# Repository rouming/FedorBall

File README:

NAME
    FedorBall -- is a toy-ball which detects current top position
    with accelerometer MMA7455 and turns on leds in special order
    using 4 led drivers TLC5940.

USED MATERIALS
    ATMEGA16
        http://www.atmel.com/Images/doc2466.pdf
        http://www.atmel.com/Images/doc8453.pdf
        http://www.tty1.net/blog/2008-04-29-avr-gcc-optimisations_en.html

    TLC5940
        http://code.google.com/p/tlc5940arduino/
        http://www.ti.com/lit/ds/symlink/tlc5940.pdf

    MMA7455
        http://arduino.cc/playground/Main/MMA7455
        http://www.freescale.com/files/sensors/doc/app_note/AN3468.pdf
        http://cache.freescale.com/files/sensors/doc/data_sheet/MMA7455L.pdf?fpsp=1

    TWI(I2C)
        http://easyelectronics.ru/avr-uchebnyj-kurs-ispolzovanie-avr-twi-dlya-raboty-s-shinoj-iic-i2c.html

    DODECAHEDRON INFO
        http://ru.wikipedia.org/wiki/Додекаэдр
        http://www.maths.surrey.ac.uk/hosted-sites/R.Knott/Fibonacci/phi3DGeom.html

    RAY-TRIANGLE INTERSECTION
        http://jgt.akpeters.com/papers/MollerTrumbore97/

    FIXED POINT
        http://gcc.gnu.org/wiki/FixedPointArithmetic
        http://x86asm.net/articles/fixed-point-arithmetic-and-tricks/

    OPENGL
        http://www.songho.ca/opengl/gl_vertexarray.html

AUTHOR
    Roman Pen

USERS
    son Fedor

ACKNOWLEDGEMENTS
COPYRIGHT & LICENSE
    Copyright 2012 Roman Pen

    This program is free software; you can redistribute it and/or modify it
    under the terms of either: the GNU General Public License as published
    by the Free Software Foundation

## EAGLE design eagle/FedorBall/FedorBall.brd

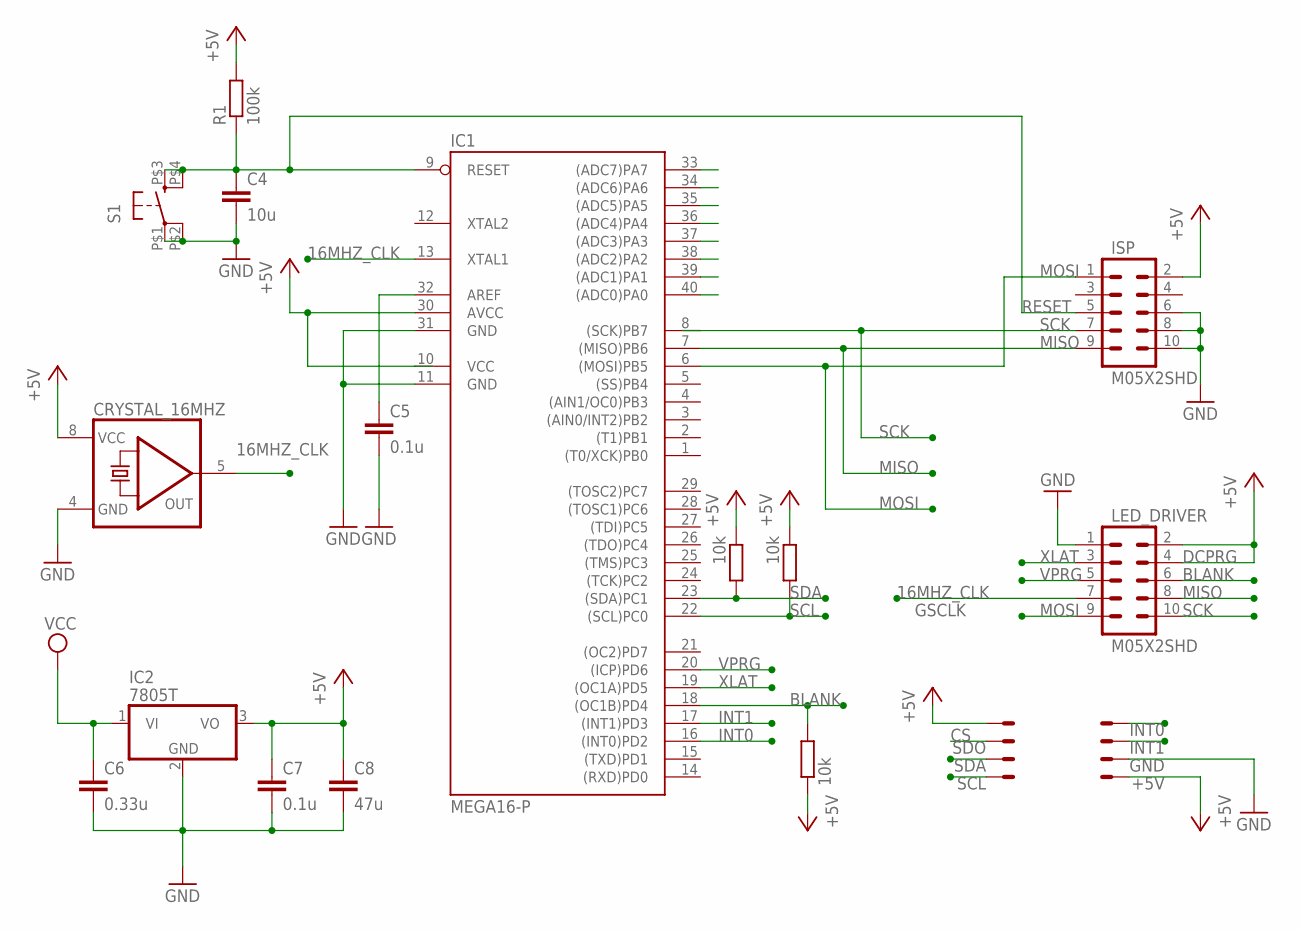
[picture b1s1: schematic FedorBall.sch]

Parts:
C4: 10u; C050-024X044
C5, C7: 0.1u; C050-024X044
C6: 0.33u; C050-024X044
C8: 47u; C050-024X044
CRYSTAL_16MHZ: QG5460; DIL08S
IC1: MEGA16-P; DIL40
IC2: 7805T; TO220H
ISP: M05X2SHD; 2X5-SHROUDED
LED_DRIVER: M05X2SHD; 2X5-SHROUDED
R1: 100k; 0207/10
R2, R5, R6: 10k; 0207/10
S1: TAC_SWITCHKSA_SEALED; KSA_SEALED_TAC_SWITCH
X1, X2: 22-23-2041

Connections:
16MHZ_CLK: CRYSTAL_16MHZ.5 (OUT), IC1.13 (XTAL1), LED_DRIVER.7
+5V: C7.1, C8.1, CRYSTAL_16MHZ.8 (VCC), IC1.10 (VCC), IC1.30 (AVCC), IC2.3 (VO), ISP.2, LED_DRIVER.2, LED_DRIVER.4, R1.2, R2.1, R5.1, R6.1, X1.1, X2.4
BLANK: IC1.18 ((OC1B)PD4), LED_DRIVER.6, R2.2
GND: C4.2, C5.2, C6.2, C7.2, C8.2, CRYSTAL_16MHZ.4 (GND), IC1.11 (GND), IC1.31 (GND), IC2.2 (GND), ISP.6, ISP.8, ISP.10, LED_DRIVER.1, S1.P$1 (1), S1.P$2 (2), X1.2
INT0: IC1.16 ((INT0)PD2), X1.4
INT1: IC1.17 ((INT1)PD3), X1.3
MISO: IC1.7 ((MISO)PB6), ISP.9, LED_DRIVER.8
MOSI: IC1.6 ((MOSI)PB5), ISP.1, LED_DRIVER.9
unnamed: C5.1, IC1.32 (AREF)
unnamed: C4.1, IC1.9 (RESET), ISP.5, R1.1, S1.P$3 (3), S1.P$4 (4)
SCK: IC1.8 ((SCK)PB7), ISP.7, LED_DRIVER.10
SCL: IC1.22 ((SCL)PC0), R6.2, X2.1
SDA: IC1.23 ((SDA)PC1), R5.2, X2.2
SDO: X2.3
VCC: C6.1, IC2.1 (VI)
VPRG: IC1.20 ((ICP)PD6), LED_DRIVER.5
XLAT: IC1.19 ((OC1A)PD5), LED_DRIVER.3

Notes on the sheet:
DCPRG
SCK
MISO
MOSI
RESET
GSCLK

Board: 2 copper layers, 17 parts (15 on the bottom side), 16 nets, no tracks yet.

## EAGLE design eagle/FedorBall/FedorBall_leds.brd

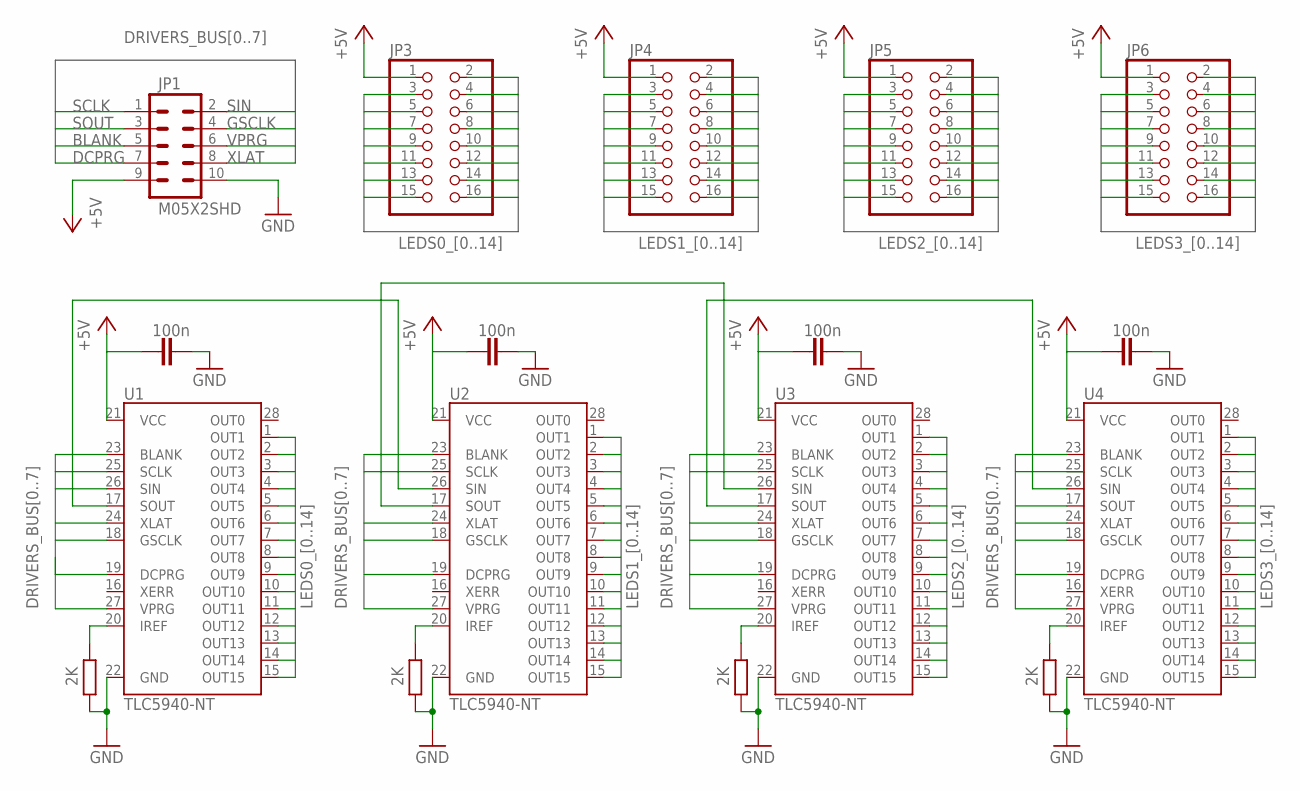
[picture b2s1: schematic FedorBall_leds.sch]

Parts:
C1, C2, C3, C4: 100n; C025-024X044
JP1: M05X2SHD; 2X5-SHROUDED
JP3, JP4, JP5, JP6: PINHD-2X8; 2X08
R1, R2, R3, R4: 2K; 0204/5
U1, U2, U3, U4: TLC5940-NT; DIL28-3

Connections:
+5V: C1.1, C2.1, C3.1, C4.1, JP1.9, JP3.1, JP4.1, JP5.1, JP6.1, U1.21 (VCC), U2.21 (VCC), U3.21 (VCC), U4.21 (VCC)
DRIVERS_BUS0: JP1.5, U1.23 (BLANK), U2.23 (BLANK), U3.23 (BLANK), U4.23 (BLANK)
DRIVERS_BUS1: JP1.1, U1.25 (SCLK), U2.25 (SCLK), U3.25 (SCLK)
DRIVERS_BUS2: JP1.2, U1.26 (SIN)
DRIVERS_BUS3: JP1.3, U4.17 (SOUT)
DRIVERS_BUS4: JP1.8, U1.24 (XLAT), U2.24 (XLAT), U3.24 (XLAT), U4.24 (XLAT)
DRIVERS_BUS5: JP1.4, U1.18 (GSCLK), U2.18 (GSCLK), U3.18 (GSCLK), U4.18 (GSCLK)
DRIVERS_BUS6: JP1.7, U1.19 (DCPRG), U2.19 (DCPRG), U3.19 (DCPRG), U4.19 (DCPRG)
DRIVERS_BUS7: JP1.6, U1.27 (VPRG), U2.27 (VPRG), U3.27 (VPRG), U4.27 (VPRG)
GND: C1.2, C2.2, C3.2, C4.2, JP1.10, R1.1, R2.1, R3.1, R4.1, U1.22 (GND), U2.22 (GND), U3.22 (GND), U4.22 (GND)
LEDS0_0: JP3.16, U1.1 (OUT1)
LEDS0_1: JP3.15, U1.2 (OUT2)
LEDS0_2: JP3.14, U1.3 (OUT3)
LEDS0_3: JP3.13, U1.4 (OUT4)
LEDS0_4: JP3.12, U1.5 (OUT5)
LEDS0_5: JP3.11, U1.6 (OUT6)
LEDS0_6: JP3.10, U1.7 (OUT7)
LEDS0_7: JP3.9, U1.8 (OUT8)
LEDS0_8: JP3.8, U1.9 (OUT9)
LEDS0_9: JP3.7, U1.10 (OUT10)
LEDS0_10: JP3.6, U1.11 (OUT11)
LEDS0_11: JP3.5, U1.12 (OUT12)
LEDS0_12: JP3.4, U1.13 (OUT13)
LEDS0_13: JP3.3, U1.14 (OUT14)
LEDS0_14: JP3.2, U1.15 (OUT15)
LEDS1_0: JP4.16, U2.1 (OUT1)
LEDS1_1: JP4.15, U2.2 (OUT2)
LEDS1_2: JP4.14, U2.3 (OUT3)
LEDS1_3: JP4.13, U2.4 (OUT4)
LEDS1_4: JP4.12, U2.5 (OUT5)
LEDS1_5: JP4.11, U2.6 (OUT6)
LEDS1_6: JP4.10, U2.7 (OUT7)
LEDS1_7: JP4.9, U2.8 (OUT8)
LEDS1_8: JP4.8, U2.9 (OUT9)
LEDS1_9: JP4.7, U2.10 (OUT10)
LEDS1_10: JP4.6, U2.11 (OUT11)
LEDS1_11: JP4.5, U2.12 (OUT12)
LEDS1_12: JP4.4, U2.13 (OUT13)
LEDS1_13: JP4.3, U2.14 (OUT14)
LEDS1_14: JP4.2, U2.15 (OUT15)
LEDS2_0: JP5.16, U3.1 (OUT1)
LEDS2_1: JP5.15, U3.2 (OUT2)
LEDS2_2: JP5.14, U3.3 (OUT3)
LEDS2_3: JP5.13, U3.4 (OUT4)
LEDS2_4: JP5.12, U3.5 (OUT5)
LEDS2_5: JP5.11, U3.6 (OUT6)
LEDS2_6: JP5.10, U3.7 (OUT7)
LEDS2_7: JP5.9, U3.8 (OUT8)
LEDS2_8: JP5.8, U3.9 (OUT9)
LEDS2_9: JP5.7, U3.10 (OUT10)
LEDS2_10: JP5.6, U3.11 (OUT11)
LEDS2_11: JP5.5, U3.12 (OUT12)
LEDS2_12: JP5.4, U3.13 (OUT13)
LEDS2_13: JP5.3, U3.14 (OUT14)
LEDS2_14: JP5.2, U3.15 (OUT15)
LEDS3_0: JP6.16, U4.1 (OUT1)
LEDS3_1: JP6.15, U4.2 (OUT2)
LEDS3_2: JP6.14, U4.3 (OUT3)
LEDS3_3: U4.4 (OUT4)
LEDS3_4: JP6.12, U4.5 (OUT5)
LEDS3_5: JP6.11, U4.6 (OUT6)
LEDS3_6: JP6.10, U4.7 (OUT7)
LEDS3_7: JP6.9, U4.8 (OUT8)
LEDS3_8: JP6.8, U4.9 (OUT9)
LEDS3_9: JP6.7, U4.10 (OUT10)
LEDS3_10: JP6.6, U4.11 (OUT11)
LEDS3_11: JP6.5, U4.12 (OUT12)
LEDS3_12: JP6.4, U4.13 (OUT13)
LEDS3_13: JP6.3, U4.14 (OUT14)
LEDS3_14: JP6.2, U4.15 (OUT15)
unnamed: U1.17 (SOUT), U2.26 (SIN)
unnamed: U2.17 (SOUT), U3.26 (SIN)
unnamed: U3.17 (SOUT), U4.26 (SIN)
unnamed: R2.2, U1.20 (IREF)
unnamed: R4.2, U2.20 (IREF)
unnamed: R3.2, U3.20 (IREF)
unnamed: R1.2, U4.20 (IREF)

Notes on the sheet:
XLAT
VPRG
GSCLK
SIN
DCPRG
BLANK
SOUT
SCLK

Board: 2 copper layers, 17 parts (16 on the bottom side), 76 nets, no tracks yet.

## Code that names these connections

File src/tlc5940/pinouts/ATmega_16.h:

#ifndef TLC_ATMEGA_16_H
#define TLC_ATMEGA_16_H

/** \file
    SPI and timer pins for the ATmega16(L).  Don't edit these.  All
    changeable pins are defined in tlc_config.h */

/** VPRG pin 20 -> VPRG (TLC pin 27) */
#define DEFAULT_VPRG_PIN    PD6
#define DEFAULT_VPRG_PORT   PORTD
#define DEFAULT_VPRG_DDR    DDRD

/** XERR pin 1 -> XERR (TLC pin 16) */
#define DEFAULT_XERR_PIN    PB0
#define DEFAULT_XERR_PORT   PORTB
#define DEFAULT_XERR_DDR    DDRB
#define DEFAULT_XERR_PINS   PINB

/** SIN pin 6 -> SIN (TLC pin 26) */
#define DEFAULT_BB_SIN_PIN      PB5
#define DEFAULT_BB_SIN_PORT     PORTB
#define DEFAULT_BB_SIN_DDR      DDRB
/** SCLK pin 8 -> SCLK (TLC pin 25) */
#define DEFAULT_BB_SCLK_PIN     PB7
#define DEFAULT_BB_SCLK_PORT    PORTB
#define DEFAULT_BB_SCLK_DDR     DDRB

/** MOSI pin 6 -> SIN (TLC pin 26) */
#define TLC_MOSI_PIN     PB5
#define TLC_MOSI_PORT    PORTB
#define TLC_MOSI_DDR     DDRB

/** SCK pin 8 -> SCLK (TLC pin 25) */
#define TLC_SCK_PIN      PB7
#define TLC_SCK_PORT     PORTB
#define TLC_SCK_DDR      DDRB

/** SS will be set to output as to not interfere with SPI master operation.
    If you have changed the pin-outs and the library doesn't seem to work
    or works intermittently, make sure this pin is set correctly.  This pin
    will not be used by the library other than setting its direction to
    output. */
#define TLC_SS_PIN       PB4
#define TLC_SS_DDR       DDRB

/** OC1A pin 19 -> XLAT (TLC pin 24) */
#define XLAT_PIN     PD5
#define XLAT_PORT    PORTD
#define XLAT_DDR     DDRD

/** OC1B pin 18 -> BLANK (TLC pin 23) */
#define BLANK_PIN    PD4
#define BLANK_PORT   PORTD
#define BLANK_DDR    DDRD

/** OC2 pin 21 -> GSCLK (TLC pin 18) */
#define GSCLK_PIN    PD7
#define GSCLK_PORT   PORTD
#define GSCLK_DDR    DDRD

#endif

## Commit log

2012-06-18 eagle scheme scratch
2012-06-19 update main scheme and board
2012-06-19 add scheme and board for leds managing
2012-06-19 continue implementing leds driver scheme
2012-06-19 remove useless eagle project file
2012-06-20 add dodecahedron OpenGL simulation sources for testing and visualizing
    sources based on OpenGL Vertex Array tutorial
    http://www.songho.ca/opengl/gl_vertexarray.html
2012-06-21 draw dodecahedron routine
2012-06-21 convert dos to unix
2012-06-28 add original cpp and updates description
2012-06-28 remove from gl sources everything useless
2012-06-28 decrease camera distance
2012-06-28 normalize dodecahedron
2012-06-28 add ray triangle intersection sources
2012-06-28 find intersection of ray on dodecahedron
2012-06-28 use original dodecahedron coords on ray intersection
2012-07-02 identation tweaks. tabs vs spaces
2012-07-02 calcalate x,y,z of camera eye and set this coords to crossing ray
2012-07-02 convert double to float for ray triangle intersection code
2012-07-02 ray-triangle intersection on fixed point
2012-07-05 schematic tweaks
2012-07-06 update scheme
2012-07-09 update leds board scheme
2012-07-12 update schematic for main board
2012-07-17 add tlc5940 sources
    this is copy of https://code.google.com/p/tlc5940arduino
2012-07-17 tune tlc5940 to work with atmega16
2012-07-17 some helpers to work with mma7455
2012-07-17 remove garbage
2012-07-17 tlc5940 port to atmega16
2012-07-17 compile tlc5940.cpp
2012-07-17 we use 4 tlc chained for fedor ball not 1
2012-07-17 rename main.c to main.cpp
2012-07-17 test tlc5940 code
2012-07-18 enable vprg
2012-07-18 enable global interrupts
2012-07-19 add makefile rule to setup ttyUSB0 correctly to communicate with mc
2012-07-19 start UART implementation
2012-07-19 add lockless ring buffer implementation (based on portaudio sources)
2012-07-19 add ring buffer to uart
2012-07-19 uart interrupt-driven implementation using ring buffer
2012-07-19 add logging file with LOG macros which uses uart_printf call
2012-07-19 init uart and use first log msg
2012-07-20 style tweaks: change function name
2012-07-20 add tty.c to test USB-UART bridge and uart implementation
2012-07-20 use external generator instead of glitchy internal oscillator
    uart does not want to work on internal oscillator!!!
2012-07-20 init uart in more standard mode: 8bit, 1stop bit, no parity
2012-07-20 tty test app tweaks
2012-07-21 connect GSCLK pin of TLC to external 16Mhz crystal
2012-07-21 reset TX ring buffer if nothing to send any more
    reset means 'start from the beginning'
    so, to avoid buffer split on two parts: bottom and half
    at the end just reset indices
2012-07-22 start implementing interrupt-driven i2c (twi in avr terms)
2012-07-23 twi interrupt driven implementation
2012-07-24 implement twi iov ops instead of plain send/recv
2012-07-24 remove useless atomic block from uart_init function. simply disable uart at start of the call.
2012-07-24 fix twi: flip nack
2012-07-24 fix uart_printf: check overflow
2012-07-24 define uart buffers in some other place, not in uart.c itself
2012-07-24 port arduino mma7455 driver to atmega16
2012-07-24 add picocom cmd to makefile
2012-07-25 update schematic and board according to last hardware experiments
2012-07-26 move raytri sources to src
    aslo update makefiles
2012-07-26 supress all 'left shift count >= width of type' warnings on avr-gcc
2012-07-26 add copyright header
2012-07-26 move fixed point math from raytri header to fixed.h
2012-07-27 again copy raytri.[ch] and fixed.h sources from ../src. because binary file for atmega16 is too big, so some raytri function will be removed.
2012-07-27 add coords.h heder with definition of arrays with coords
2012-07-27 remove some garbage from GL dodecahedron coords definitions
2012-07-27 make single header atomic.h for memory berrier declaration
2012-07-29 describe leds on ball with their indices
2012-07-31 normalize dodecahedron coords and rotate it on 31.717 angle around X axis to have bottom face on X plane
2012-07-31 replace original dodacahedron verteces with rotated verteces from gl_dodacahedron_src
2012-08-01 add map of dodecahedron vertexes to real tlc pinouts
2012-08-01 draw index of every vertex on dodecahedron
2012-08-01 fix tlc index in comment
2012-08-01 add some std includes to ring_buffer.h
2012-08-01 add extern "C" to raytri.h
2012-08-01 turn off other intersects algorithms with special macroses
    with all this stuff compiled binary is > 16K
    and it is not able to fit into MC
2012-08-01 add binary_stat.pl for getting rom/ram stat from fedorball.elf
2012-08-01 code size optimization, part 2
    rename int32->int16
    rename int32->int8
    twi.h
    twi.c
    Program: 12264 bytes (74.9% full)
    (.text, .data, .bootloader)
2012-08-01 code size optimization, part 1
    rename int32->int16
    ring_buffer.h
    uart.h
    uart.c
    main.cpp
    Program: 13202 bytes (80.6% full)
2012-08-01 code size optimization, part 3
    add compiler and linker flags taken from
    http://www.tty1.net/blog/2008-04-29-avr-gcc-optimisations_en.html
    Atmel AVR4027: Tips and Tricks to Optimize Your C Code for 8-bit AVR Microcontrollers
    Program: 8462 bytes (51.6% full)
    (.text, .data, .bootloader)
    Data: 562 bytes (54.9% full)
2012-08-01 again use raytri and fixes sources from ../src
2012-08-01 add std.h with some std defines
2012-08-01 reduce fixed point precision from 16 bit to 8 to reduce code size generation
    also reduce prevision of fixed epsilon error, because for 8 bit
    it become zero
2012-08-02 fixed point math does not require any epsilon errors, just check that value is not zero
2012-08-02 add ITOFP conversion macros to fixed.h
2012-08-02 add macros ARRAY_SIZE to std.h for easy array size calculation
2012-08-02 turn on fixed math for ray-triangle intersection raytri.c algo
2012-08-02 implement scratch of main algorithm of searching intersection of x,y,z acceleration with any face of dodecahedron face
2012-08-02 compiller does not calculate correctly fp_to_f, so calculate it in gl_dodecahedron app and copy output to coords.h
2012-08-02 map accel coords system to gl coords system, yzx -> xyz
    also invert accel z coord
2012-08-02 update log message about found face
2012-08-02 reduce delay from 1s to 0.1s
2012-08-09 RAM size optimization: now all strings for logging is placed in program memory space.
2012-08-09 made mistake while real assembling of fedor ball -> advance indices for #2 tlc on 1
2012-08-13 top leds must be anticlockwise, not clockwise. do swap
2012-08-13 comments tweaks: change scheme of leds on dodecahedron
2012-08-13 add faces to dodecahedron schema and test faces coords and implement faces walking test
2012-08-13 remove useless test code
2012-08-13 fix faces walking test
2012-08-15 rename main loop call
2012-08-15 tweaks: increase ball freq from 10 to 50 hz, make red color to be dim
2012-08-15 minor scheme changes
2012-08-15 put mcu to sleep if accel does not report x,y,z changes > threshold for 30 seconds
    mcu will be waken up by external interrupt from accel, which will be put
    in pulse mode before mcu sleep
2012-08-17 do not stop other timers while setting/unsetting XLAT timer
2012-08-17 enable only int1 interrupt and implement empty int1 handler
2012-08-17 fix mma7455 init procedure: forgotten mode set
2012-08-17 enable uart disable/enable calls
2012-08-17 fix goto sleep routine: switch accel to level detection mode, stop timers and uart before sleep
2012-08-17 change color component on new face
2012-08-20 add used materials links to readme file

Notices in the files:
parts and their libraries:
SparkFun: Licensing: CC v3.0 Share-Alike You are welcome to use this library for commercial purposes.
